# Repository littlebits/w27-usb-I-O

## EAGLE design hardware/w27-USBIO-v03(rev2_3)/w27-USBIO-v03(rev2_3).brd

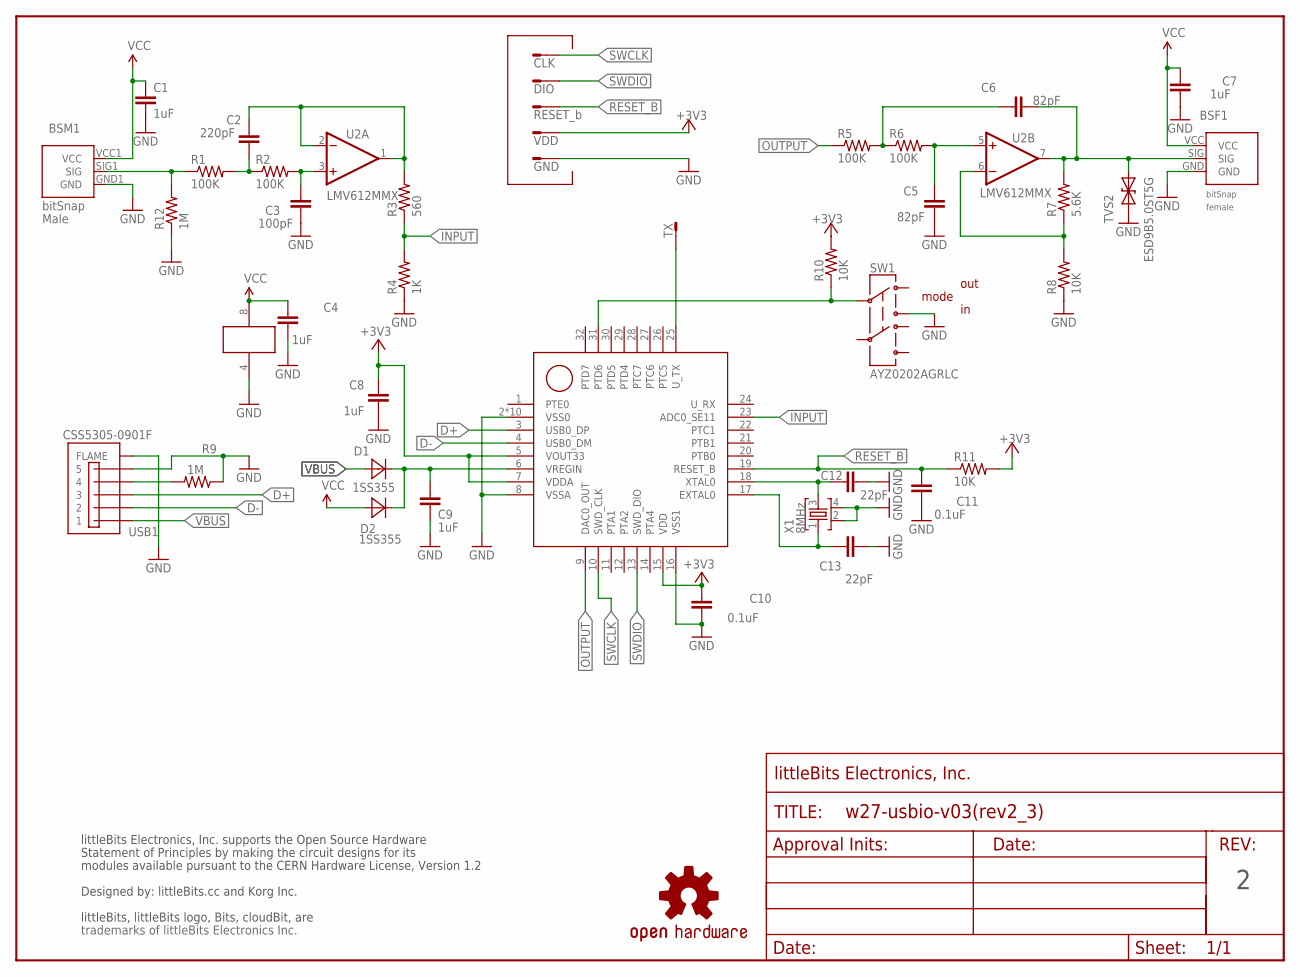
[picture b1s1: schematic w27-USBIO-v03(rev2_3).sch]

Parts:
BSF1: BITSNAP_V03_FEMALE
BSM1: BITSNAP_V03_MALE
C1, C4, C7, C8, C9: 1uF; CC_1608_0.8_TBR_LB_1PRIMARY
C2: 220pF; CC_1608_0.8_TBR_LB_1PRIMARY
C3: 100pF; CC_1608_0.8_TBR_LB_1PRIMARY
C5, C6: 82pF; CC_1608_0.8_TBR_LB_1PRIMARY
C10, C11: 0.1uF; CC_1608_0.8_TBR_LB_1PRIMARY
C12, C13: 22pF; CC_1608_0.8_TBR_LB_1PRIMARY
D1, D2: 1SS355; DISC_ROHM-UMD2_#_TBR_LB_1PRIMARY
FRAME1: FRAME-LETTER-OHWOHW; FABDWG01-OHW
JP1: GND; TEST_POINT_1PRIMARY
JP2: VDD; TEST_POINT_1PRIMARY
JP3: RESET_b; TEST_POINT_1PRIMARY
JP4: DIO; TEST_POINT_1PRIMARY
JP5: CLK; TEST_POINT_1PRIMARY
JP6: TX; TEST_POINT_1PRIMARY
R1, R2, R5, R6: 100K; R_1608_LB
R3: 560; R_1608_LB
R4: 1K; R_1608_LB
R7: 5.6K; R_1608_LB
R8, R10, R11: 10K; R_1608_LB
R9: 1M; R_1608_LB
R12: 1M; RES-0402
SW1: AYZ0202AGRLC; SW_MS-22C01_#_TBR_LB_1PRIMARY
TVS2: ESD9B5.0ST5G; SOD-923
U1: MKL26Z64VFM4; IC_TI-QFN32_0.5_TBR_LB_1PRIMARY
U2: LMV612MMX; IC_TSSOP8-DCK_0.65_TBR_LB_1PRIMARY
U$1: OSHWCREDIT-KORG
U$5: OSHW-LOGOL; OSHW-LOGO-L
USB1: CSS5305-0901F; MICRO-USB-FRONT-DIP-REAR-SMD
X1: 8MHz; X_ROSON_RT5_#_TBR_LB_1PRIMARY

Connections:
+3V3: C8.2, C10.2, JP2.1, R10.2, R11.2, U1.5 (VOUT33), U1.7 (VDDA), U1.15 (VDD)
D+: U1.3 (USB0_DP), USB1.3
D-: U1.4 (USB0_DM), USB1.2
GND: BSF1.GND, BSM1.GND1 (GND), C1.2, C3.1, C4.1, C5.1, C7.1, C8.1, C9.2, C10.1, C11.1, C12.1, C13.1, JP1.1, R4.1, R8.1, R9.1, R12.1, SW1.3, TVS2.1 (A), U1.2 (VSS0), U1.8 (VSSA), U1.16 (VSS1), U1.33 (VSS0), U1.34 (VSS0), U1.35 (VSS0), U1.36 (VSS0), U1.37 (VSS0), U1.38 (VSS0), U1.39 (VSS0), U1.40 (VSS0), U1.41 (VSS0), U2.4 (V-), USB1.5, USB1.6 (FLAME), USB1.7 (FLAME), USB1.8 (FLAME), USB1.9 (FLAME), USB1.10 (FLAME), USB1.11 (FLAME), X1.2, X1.4
INPUT: R3.1, R4.2, U1.23 (ADC0_SE11)
unnamed: BSM1.SIG1 (SIG), R1.1, R12.2
unnamed: C2.2, R3.2, U2.1 (OUT), U2.2 (-IN)
unnamed: C3.2, R2.2, U2.3 (+IN)
unnamed: C2.1, R1.2, R2.1
unnamed: R10.1, SW1.2, U1.31 (PTD6)
unnamed: BSF1.SIG, C6.2, R7.2, TVS2.2 (C), U2.7 (OUT)
unnamed: C9.1, D1.2, D2.2, U1.6 (VREGIN)
unnamed: C6.1, R5.2, R6.1
unnamed: C5.2, R6.2, U2.5 (+IN)
unnamed: R9.2, USB1.4
unnamed: C13.2, U1.17 (EXTAL0), X1.1
unnamed: C12.2, U1.18 (XTAL0), X1.3
unnamed: R7.1, R8.2, U2.6 (-IN)
OUTPUT: R5.1, U1.9 (DAC0_OUT)
RESET_B: C11.2, JP3.1, R11.1, U1.19 (RESET_B)
SWCLK: JP5.1, U1.10 (SWD_CLK)
SWDIO: JP4.1, U1.13 (SWD_DIO)
TX: JP6.1, U1.25 (U_TX)
VBUS: D1.1, USB1.1
VCC: BSF1.VCC, BSM1.VCC1 (VCC), C1.1, C4.2, C7.2, D2.1, U2.8 (V+)

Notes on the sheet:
out
mode

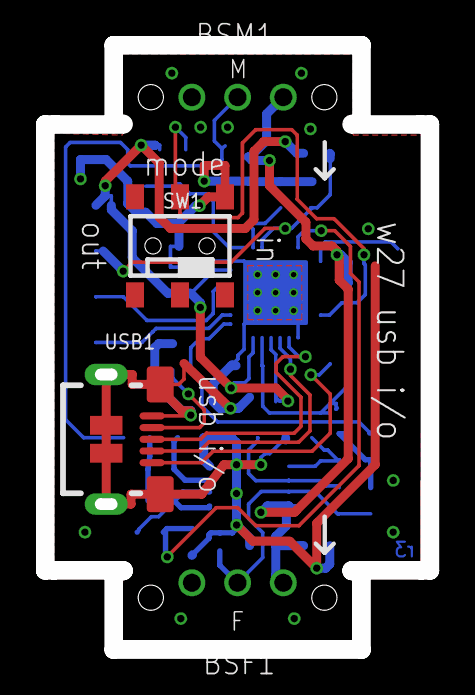
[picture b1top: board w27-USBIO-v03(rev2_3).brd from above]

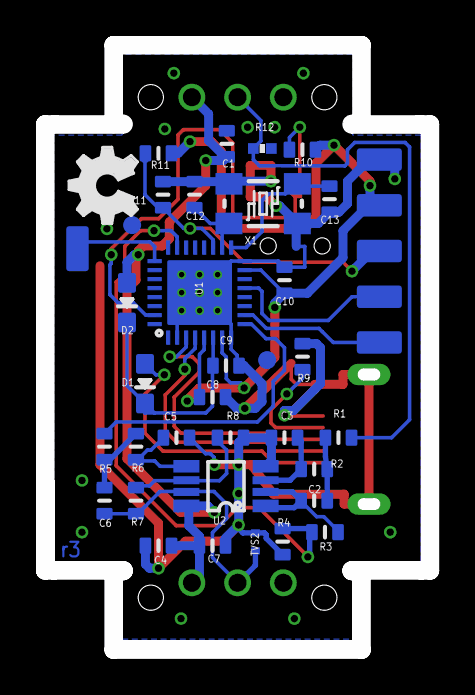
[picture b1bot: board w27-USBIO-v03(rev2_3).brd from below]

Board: 2 copper layers, 21.4 x 33.6 mm, 45 parts (37 on the bottom side), 25 nets.

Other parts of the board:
E$1: OSHW_FILLX150_NOTEXT

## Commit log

2015-04-21 First commit, added hardware files

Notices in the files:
parts and their libraries:
LITTLEBITS: modules available pursuant to the CERN Hardware License, Version 1.2
